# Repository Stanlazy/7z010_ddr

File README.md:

# 4-Layer XC7Z010 DDR3 Layout

A compact layout of XC7Z010 with DDR3.

Tested with DDR3L-1066 on PCB manufactured by JLC.

Traces are length matched to ±0.5mm with board thickness of 1.2mm

Package delay's equivalent length are calculated with dielectric constant of 4.05.

Traces are cutting reference plane? It works.™

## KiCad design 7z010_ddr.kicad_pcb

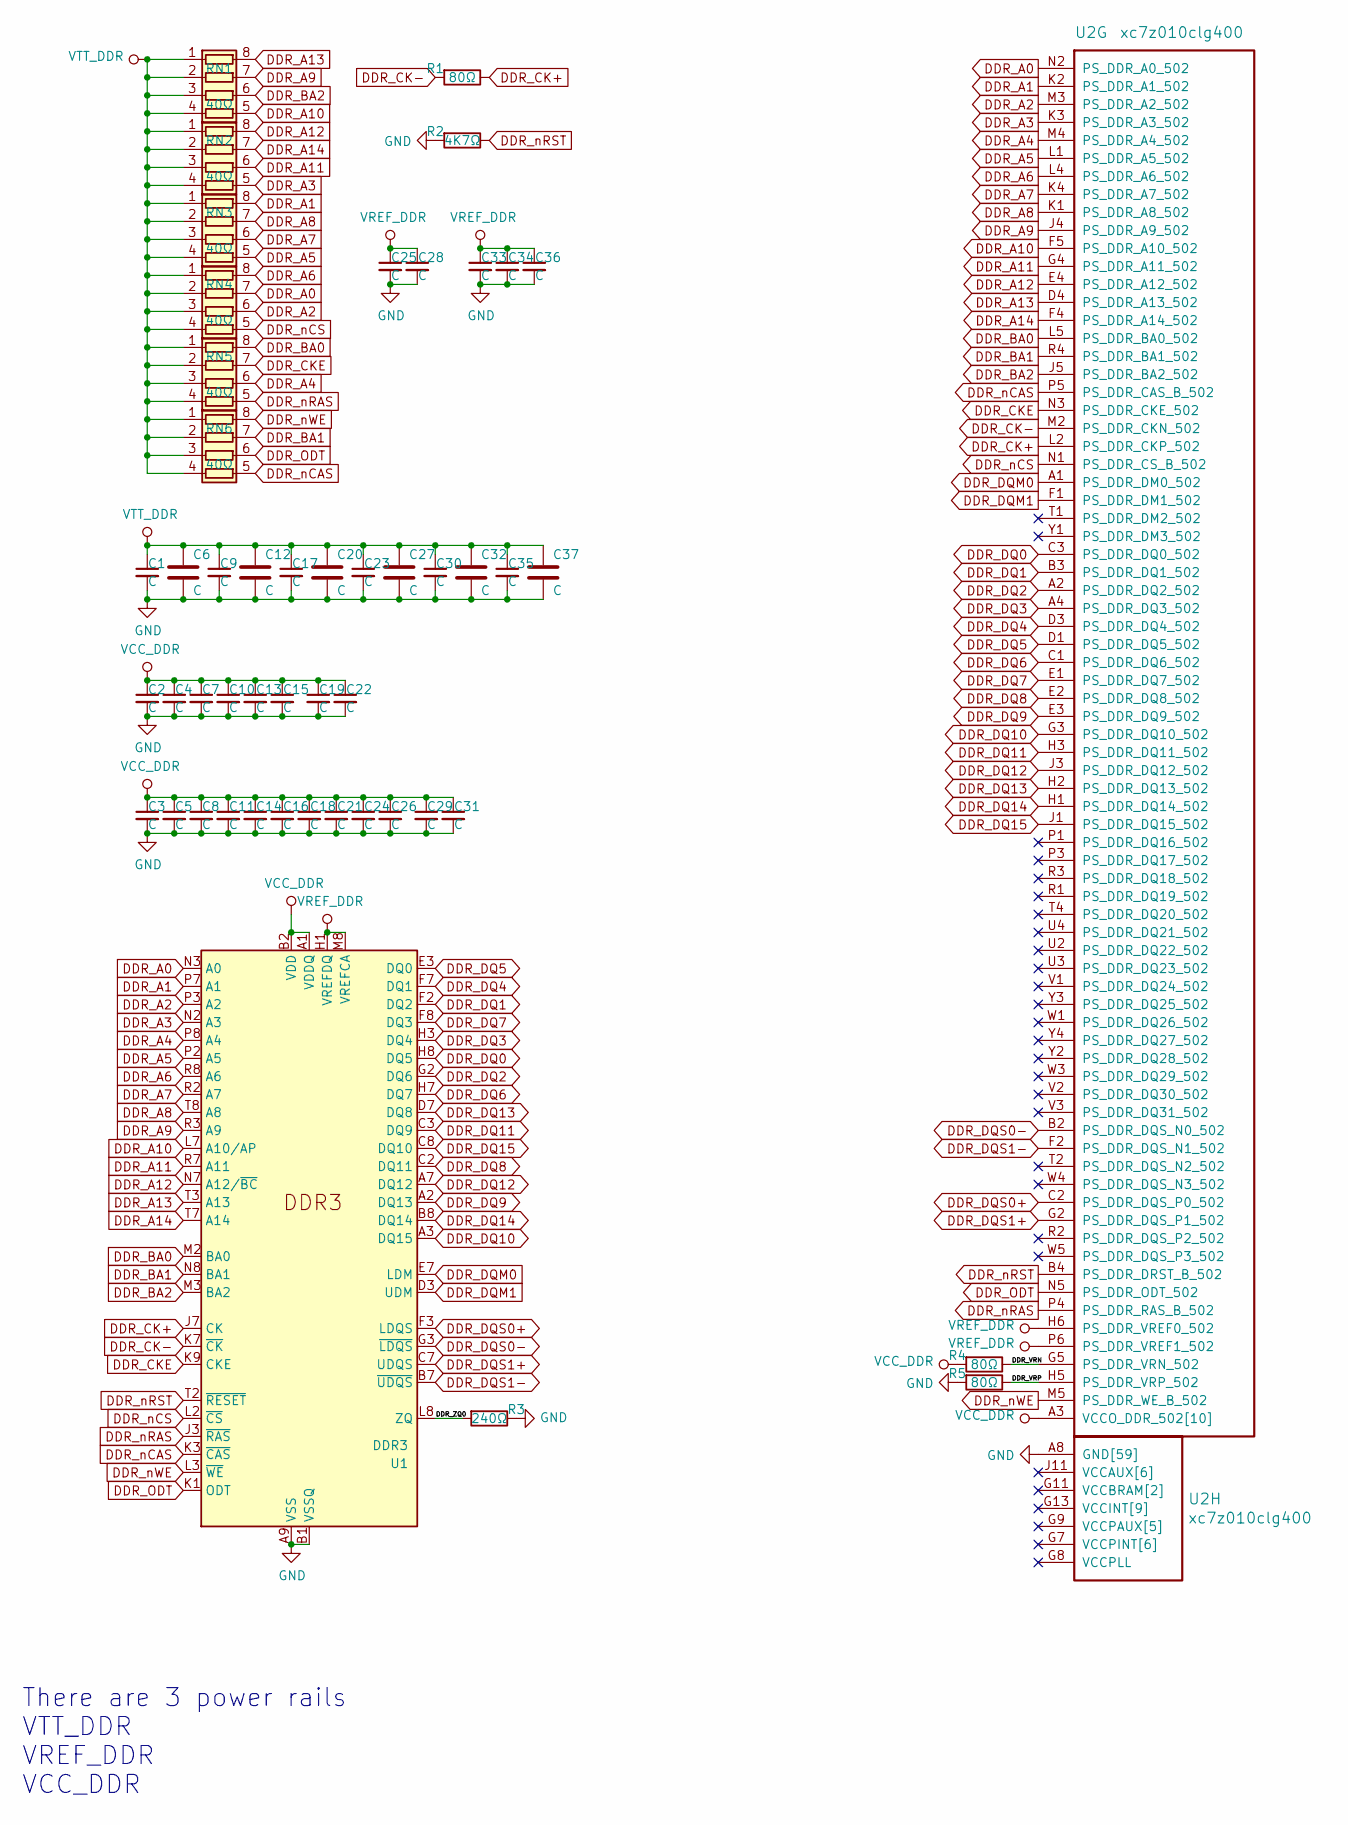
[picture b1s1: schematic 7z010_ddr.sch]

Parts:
C1, C2, C3, C4, C5, C7, C8, C9, C10, C11, C13, C14, C15, C16, C17, C18, C21, C23, C24, C25, C26, C28, C30, C33, C34, C35: C; C_0201_0603Metric
C6, C12, C20, C27, C32, C36, C37: C; C_0402_1005Metric
C19, C22, C29, C31: C; C_0201_0603Metric_WideGap
R1, R4, R5: 80Ω; R_0201_0603Metric
R2: 4K7Ω; R_0201_0603Metric
R3: 240Ω; R_0201_0603Metric
RN1, RN2, RN3, RN4, RN5, RN6: 40Ω; R_Array_Convex_4x0402
U1: DDR3; BGA-96_9.0x13.0mm_Layout2x3x16_P0.8mm_NoPaste
U2: xc7z010clg400; Xilinx_CLG400_NoPaste_JLC_Package_Delay

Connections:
/DDR_VRN: R4.1, U2.G5 (PS_DDR_VRN_502)
/DDR_VRP: R5.1, U2.H5 (PS_DDR_VRP_502)
/DDR_ZQ0: R3.2, U1.L8 (ZQ)
DDR_A0: RN4.7 (R2.2), U1.N3 (A0), U2.N2 (PS_DDR_A0_502)
DDR_A1: RN3.8 (R1.2), U1.P7 (A1), U2.K2 (PS_DDR_A1_502)
DDR_A2: RN4.6 (R3.2), U1.P3 (A2), U2.M3 (PS_DDR_A2_502)
DDR_A3: RN2.5 (R4.2), U1.N2 (A3), U2.K3 (PS_DDR_A3_502)
DDR_A4: RN5.6 (R3.2), U1.P8 (A4), U2.M4 (PS_DDR_A4_502)
DDR_A5: RN3.5 (R4.2), U1.P2 (A5), U2.L1 (PS_DDR_A5_502)
DDR_A6: RN4.8 (R1.2), U1.R8 (A6), U2.L4 (PS_DDR_A6_502)
DDR_A7: RN3.6 (R3.2), U1.R2 (A7), U2.K4 (PS_DDR_A7_502)
DDR_A8: RN3.7 (R2.2), U1.T8 (A8), U2.K1 (PS_DDR_A8_502)
DDR_A9: RN1.7 (R2.2), U1.R3 (A9), U2.J4 (PS_DDR_A9_502)
DDR_A10: RN1.5 (R4.2), U1.L7 (A10/AP), U2.F5 (PS_DDR_A10_502)
DDR_A11: RN2.6 (R3.2), U1.R7 (A11), U2.G4 (PS_DDR_A11_502)
DDR_A12: RN2.8 (R1.2), U1.N7 (A12/~BC), U2.E4 (PS_DDR_A12_502)
DDR_A13: RN1.8 (R1.2), U1.T3 (A13), U2.D4 (PS_DDR_A13_502)
DDR_A14: RN2.7 (R2.2), U1.T7 (A14), U2.F4 (PS_DDR_A14_502)
DDR_BA0: RN5.8 (R1.2), U1.M2 (BA0), U2.L5 (PS_DDR_BA0_502)
DDR_BA1: RN6.7 (R2.2), U1.N8 (BA1), U2.R4 (PS_DDR_BA1_502)
DDR_BA2: RN1.6 (R3.2), U1.M3 (BA2), U2.J5 (PS_DDR_BA2_502)
DDR_CK+: R1.1, U1.J7 (CK), U2.L2 (PS_DDR_CKP_502)
DDR_CK-: R1.2, U1.K7 (~CK), U2.M2 (PS_DDR_CKN_502)
DDR_CKE: RN5.7 (R2.2), U1.K9 (CKE), U2.N3 (PS_DDR_CKE_502)
DDR_DQ0: U1.H8 (DQ5), U2.C3 (PS_DDR_DQ0_502)
DDR_DQ1: U1.F2 (DQ2), U2.B3 (PS_DDR_DQ1_502)
DDR_DQ2: U1.G2 (DQ6), U2.A2 (PS_DDR_DQ2_502)
DDR_DQ3: U1.H3 (DQ4), U2.A4 (PS_DDR_DQ3_502)
DDR_DQ4: U1.F7 (DQ1), U2.D3 (PS_DDR_DQ4_502)
DDR_DQ5: U1.E3 (DQ0), U2.D1 (PS_DDR_DQ5_502)
DDR_DQ6: U1.H7 (DQ7), U2.C1 (PS_DDR_DQ6_502)
DDR_DQ7: U1.F8 (DQ3), U2.E1 (PS_DDR_DQ7_502)
DDR_DQ8: U1.C2 (DQ11), U2.E2 (PS_DDR_DQ8_502)
DDR_DQ9: U1.A2 (DQ13), U2.E3 (PS_DDR_DQ9_502)
DDR_DQ10: U1.A3 (DQ15), U2.G3 (PS_DDR_DQ10_502)
DDR_DQ11: U1.C3 (DQ9), U2.H3 (PS_DDR_DQ11_502)
DDR_DQ12: U1.A7 (DQ12), U2.J3 (PS_DDR_DQ12_502)
DDR_DQ13: U1.D7 (DQ8), U2.H2 (PS_DDR_DQ13_502)
DDR_DQ14: U1.B8 (DQ14), U2.H1 (PS_DDR_DQ14_502)
DDR_DQ15: U1.C8 (DQ10), U2.J1 (PS_DDR_DQ15_502)
DDR_DQM0: U1.E7 (LDM), U2.A1 (PS_DDR_DM0_502)
DDR_DQM1: U1.D3 (UDM), U2.F1 (PS_DDR_DM1_502)
DDR_DQS0+: U1.F3 (LDQS), U2.C2 (PS_DDR_DQS_P0_502)
DDR_DQS0-: U1.G3 (~LDQS), U2.B2 (PS_DDR_DQS_N0_502)
DDR_DQS1+: U1.C7 (UDQS), U2.G2 (PS_DDR_DQS_P1_502)
DDR_DQS1-: U1.B7 (~UDQS), U2.F2 (PS_DDR_DQS_N1_502)
DDR_ODT: RN6.6 (R3.2), U1.K1 (ODT), U2.N5 (PS_DDR_ODT_502)
DDR_nCAS: RN6.5 (R4.2), U1.K3 (~CAS), U2.P5 (PS_DDR_CAS_B_502)
DDR_nCS: RN4.5 (R4.2), U1.L2 (~CS), U2.N1 (PS_DDR_CS_B_502)
DDR_nRAS: RN5.5 (R4.2), U1.J3 (~RAS), U2.P4 (PS_DDR_RAS_B_502)
DDR_nRST: R2.1, U1.T2 (~RESET), U2.B4 (PS_DDR_DRST_B_502)
DDR_nWE: RN6.8 (R1.2), U1.L3 (~WE), U2.M5 (PS_DDR_WE_B_502)
GND: C1.2, C2.2, C3.2, C4.2, C5.2, C6.2, C7.2, C8.2, C9.2, C10.2, C11.2, C12.2, C13.2, C14.2, C15.2, C16.2, C17.2, C18.2, C19.2, C20.2, C21.2, C22.2, C23.2, C24.2, C25.2, C26.2, C27.2, C28.2, C29.2, C30.2, C31.2, C32.2, C33.2, C34.2, C35.2, C36.2, C37.2, R2.2, R3.1, R5.2, U1.A9 (VSS), U1.B1 (VSSQ), U1.B3 (VSS), U1.B9 (VSSQ), U1.D1 (VSSQ), U1.D8 (VSSQ), U1.E1 (VSS), U1.E2 (VSSQ), U1.E8 (VSSQ), U1.F9 (VSSQ), U1.G1 (VSSQ), U1.G8 (VSS), U1.G9 (VSSQ), U1.J2 (VSS), U1.J8 (VSS), U1.M1 (VSS), U1.M9 (VSS), U1.P1 (VSS), U1.P9 (VSS), U1.T1 (VSS), U1.T9 (VSS), U2.A8 (GND[59]), U2.A18 (GND[59]), U2.B1 (GND[59]), U2.B11 (GND[59]), U2.C4 (GND[59]), U2.C9 (GND[59]), U2.C14 (GND[59]), U2.D17 (GND[59]), U2.E10 (GND[59]), U2.E20 (GND[59]), U2.F3 (GND[59]), U2.F7 (GND[59]), U2.G10 (GND[59]), U2.G12 (GND[59]), U2.G16 (GND[59]), U2.H7 (GND[59]), U2.H9 (GND[59]), U2.H11 (GND[59]), U2.H13 (GND[59]), U2.H19 (GND[59]), U2.J2 (GND[59]), U2.J8 (GND[59]), U2.J12 (GND[59]), U2.K5 (GND[59]), U2.K7 (GND[59]), U2.K11 (GND[59]), U2.K13 (GND[59]), U2.K15 (GND[59]), U2.L8 (GND[59]), U2.L12 (GND[59]), U2.L18 (GND[59]), U2.M1 (GND[59]), U2.M7 (GND[59]), U2.M11 (GND[59]), U2.M13 (GND[59]), U2.N4 (GND[59]), U2.N8 (GND[59]), U2.N10 (GND[59]), U2.N12 (GND[59]), U2.N14 (GND[59]), U2.P7 (GND[59]), U2.P9 (GND[59]), U2.P11 (GND[59]), U2.P13 (GND[59]), U2.P17 (GND[59]), U2.R8 (GND[59]), U2.R12 (GND[59]), U2.R20 (GND[59]), U2.T3 (GND[59]), U2.T7 (GND[59]), U2.T13 (GND[59]), U2.U6 (GND[59]), U2.U16 (GND[59]), U2.V9 (GND[59]), U2.V19 (GND[59]), U2.W2 (GND[59]), U2.W12 (GND[59]), U2.Y5 (GND[59]), U2.Y15 (GND[59])
unnamed: U2.F8 (VCCPAUX[5]), U2.G9 (VCCPAUX[5]), U2.H8 (VCCPAUX[5]), U2.K8 (VCCPAUX[5]), U2.M8 (VCCPAUX[5])
unnamed: U2.G7 (VCCPINT[6]), U2.J7 (VCCPINT[6]), U2.L7 (VCCPINT[6]), U2.N7 (VCCPINT[6]), U2.P8 (VCCPINT[6]), U2.R7 (VCCPINT[6])
unnamed: U2.G11 (VCCBRAM[2]), U2.H10 (VCCBRAM[2])
unnamed: U2.G13 (VCCINT[9]), U2.H12 (VCCINT[9]), U2.J13 (VCCINT[9]), U2.K12 (VCCINT[9]), U2.L13 (VCCINT[9]), U2.M12 (VCCINT[9]), U2.N13 (VCCINT[9]), U2.P12 (VCCINT[9]), U2.R13 (VCCINT[9])
unnamed: U2.J11 (VCCAUX[6]), U2.L11 (VCCAUX[6]), U2.N9 (VCCAUX[6]), U2.N11 (VCCAUX[6]), U2.P10 (VCCAUX[6]), U2.R9 (VCCAUX[6])
VCC_DDR: C2.1, C3.1, C4.1, C5.1, C7.1, C8.1, C10.1, C11.1, C13.1, C14.1, C15.1, C16.1, C18.1, C19.1, C21.1, C22.1, C24.1, C26.1, C29.1, C31.1, R4.2, U1.A1 (VDDQ), U1.A8 (VDDQ), U1.B2 (VDD), U1.C1 (VDDQ), U1.C9 (VDDQ), U1.D2 (VDDQ), U1.D9 (VDD), U1.E9 (VDDQ), U1.F1 (VDDQ), U1.G7 (VDD), U1.H2 (VDDQ), U1.H9 (VDDQ), U1.K2 (VDD), U1.K8 (VDD), U1.N1 (VDD), U1.N9 (VDD), U1.R1 (VDD), U1.R9 (VDD), U2.A3 (VCCO_DDR_502[10]), U2.D2 (VCCO_DDR_502[10]), U2.E5 (VCCO_DDR_502[10]), U2.G1 (VCCO_DDR_502[10]), U2.H4 (VCCO_DDR_502[10]), U2.L3 (VCCO_DDR_502[10]), U2.P2 (VCCO_DDR_502[10]), U2.R5 (VCCO_DDR_502[10]), U2.U1 (VCCO_DDR_502[10]), U2.V4 (VCCO_DDR_502[10])
VREF_DDR: C25.1, C28.1, C33.1, C34.1, C36.1, U1.H1 (VREFDQ), U1.M8 (VREFCA), U2.H6 (PS_DDR_VREF0_502), U2.P6 (PS_DDR_VREF1_502)
VTT_DDR: C1.1, C6.1, C9.1, C12.1, C17.1, C20.1, C23.1, C27.1, C30.1, C32.1, C35.1, C37.1, RN1.1 (R1.1), RN1.2 (R2.1), RN1.3 (R3.1), RN1.4 (R4.1), RN2.1 (R1.1), RN2.2 (R2.1), RN2.3 (R3.1), RN2.4 (R4.1), RN3.1 (R1.1), RN3.2 (R2.1), RN3.3 (R3.1), RN3.4 (R4.1), RN4.1 (R1.1), RN4.2 (R2.1), RN4.3 (R3.1), RN4.4 (R4.1), RN5.1 (R1.1), RN5.2 (R2.1), RN5.3 (R3.1), RN5.4 (R4.1), RN6.1 (R1.1), RN6.2 (R2.1), RN6.3 (R3.1), RN6.4 (R4.1)

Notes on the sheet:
There are 3 power rails VTT_DDR VREF_DDR VCC_DDR

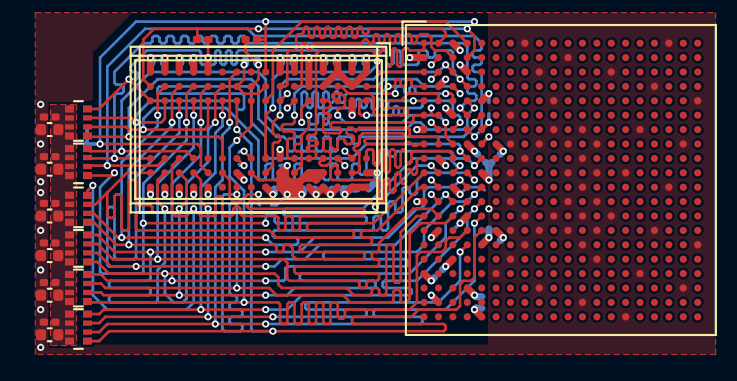
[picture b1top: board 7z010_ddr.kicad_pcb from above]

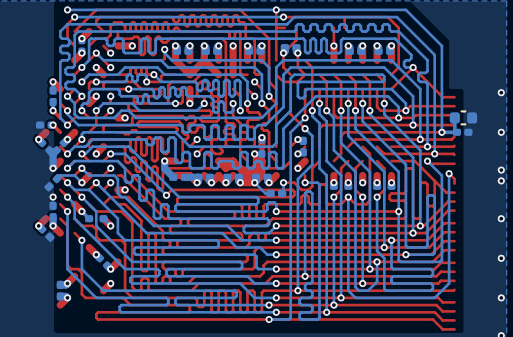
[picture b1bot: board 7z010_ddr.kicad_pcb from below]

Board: 4 copper layers, 50 parts (28 on the bottom side), 61 nets.

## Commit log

2021-11-24 initial upload
2021-11-24 update termination resistor value
2021-11-25 added GND back to sch
2021-11-25 remove cache lib
2021-11-25 move symbols to project library
2021-11-25 fix power rail junction

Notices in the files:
7z010_ddr.kicad_pcb:
GPL
